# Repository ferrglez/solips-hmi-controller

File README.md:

# SOLIPS HMI Controller — Rev A

**Hardware design · KiCad · Engineering review pending**

> **Status:** Rev A design submitted for peer review. **Not approved for fabrication.** ERC/DRC were reported clean in the working KiCad project; electrical, mechanical and physical validation are still pending.

## Overview

SOLIPS HMI Controller Rev A is a dedicated four-layer PCB intended to offload the graphical human–machine interface (HMI) from an Arduino UNO Q host. The host provides semantic application data; the STM32 executes the graphical application locally and drives a GC9A01 circular TFT display.

The design follows the engineering baseline dated **30 September 2026**. That document freezes the major architecture but explicitly leaves component-specific verification and fabrication gates open. The current KiCad implementation must be compared with that baseline during review.

## System architecture

```text
Arduino UNO Q / QRB2210 (Debian)
           │ USB 2.0
           ▼
CP2102C-A01-GQFN24 (USB–UART bridge)
           │ USART1 · 3.3 V · PA9/PA10
           ▼
STM32U585CIT6 (LQFP48)
           │ SPI1 + DMA
           ▼
GC9A01 · 240 × 240 · RGB565
```

**Design rationale:** The UNO Q retains system and application logic, while the dedicated STM32 handles `VehicleState`, `UIManager`, LVGL and graphical assets. This reduces the HMI rendering workload on the host. Firmware migration and performance are **not yet demonstrated on this PCB**.

## Key engineering choices

| Subsystem | Rev A baseline | Rationale / verification |
| --- | --- | --- |
| Main MCU | STM32U585CIT6, LQFP48 | Dedicated local HMI processing; confirm package pinout, power domains and firmware budget |
| Host interface | CP2102C-A01-GQFN24 | USB–UART with DTR/RTS for planned boot/reset control; validate electrical implementation |
| Serial | USART1 on PA9/PA10 | Shared application communication and planned ROM bootloader update path |
| Display | GC9A01, 240×240, RGB565 | SPI1 + DMA, write-only interface; confirm actual module and connector pinout |
| Supply | USB 5 V input; 3.3 V LDO ≥500 mA | Simpler bring-up and no switching regulator; confirm load, inrush and thermal budget |
| Debug | SWD, manual BOOT/RESET | Recovery path independent of the USB bridge |
| PCB | 4 layers | Top signals/components, inner GND reference, inner power, bottom signals; verify actual stackup and return paths |

## KiCad project organization

The schematic is organized into five hierarchical sheets:

1. `01_POWER.kicad_sch` — USB input and regulation
2. `02_USB_UART.kicad_sch` — USB-C and CP2102C
3. `03_MCU.kicad_sch` — STM32 and boot/reset control
4. `04_DISPLAY.kicad_sch` — GC9A01 interface
5. `05_DEBUG.kicad_sch` — SWD and manual controls

The **current authoritative KiCad files** should be placed in `hardware/`, including the top-level `.kicad_sch`, `.kicad_pcb`, `.kicad_pro`, all five hierarchical sheets, and any required custom symbol/footprint libraries or board rules. The duplicate `- copia` folder is a local backup, not a second design release.

## Layout and routing

- Four-layer PCB with inner reference and power planes.
- Placement and routing performed in KiCad; FreeRouting was used as a routing aid, followed by manual completion and DRC cleanup.
- USB D+/D−, ground continuity, via transitions, connector orientation and mechanical fit still require an engineering review.
- The most recent DRC/ERC status was reported as clean by the designer; review the committed `DRC.rpt` / `ERC.rpt` and confirm they were generated **after the final edits**.

## Review checklist

- [ ] Cross-check actual KiCad schematic against STM32U585CIT6 and CP2102C manufacturer datasheets
- [ ] Verify USB-C CC resistors, ESD, USB data routing, shield and VBUS protection
- [ ] Verify MCU VDD/VDDA/VCAP and all decoupling connections
- [ ] Validate LDO part, USB current budget and worst-case thermal dissipation
- [ ] Verify DTR/RTS–BOOT0/NRST polarity, default states and STM32 option bytes
- [ ] Verify SWD header orientation and physical accessibility
- [ ] Confirm GC9A01 **actual module** pinout, supply, backlight and connector geometry/orientation
- [ ] Check actual four-layer stackup, copper returns, clearances and manufacturability
- [ ] Regenerate ERC/DRC on the final committed project
- [ ] Close fabrication gates FG-01 / FG-02 / FG-03 with evidence

## Planned validation

The baseline defines T01–T11: power, USB enumeration, UART, SWD, manual and automatic bootloader, CLI flashing, application boot, display, HMI screens and host protocol. **These are planned tests, not completed tests.**

## Documentation

- [`docs/Engineering_Specification.docx`](docs/Engineering_Specification.docx) — original engineering requirements and schematic baseline (v1.0, 2026-09-30).

## Review request

**Requested decision:** `APPROVED FOR NEXT STAGE` / `CHANGES REQUIRED` / `NOT APPROVED`.

**No fabrication order should be placed until the open electrical, mechanical and fabrication-gate checks are resolved.**

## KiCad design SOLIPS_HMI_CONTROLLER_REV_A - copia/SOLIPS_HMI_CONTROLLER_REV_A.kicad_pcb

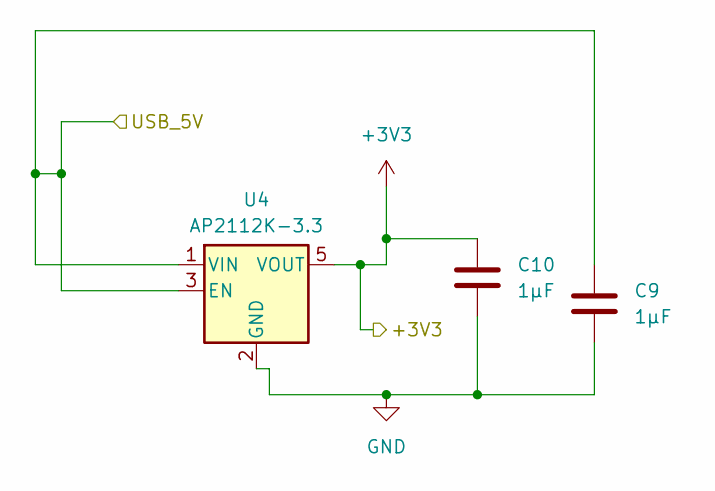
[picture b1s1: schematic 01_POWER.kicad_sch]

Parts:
C9, C10: 1µF; C_0805_2012Metric
U4: AP2112K-3.3; SOT-23-5

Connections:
+3V3: C10.1, U4.5 (VOUT); also elsewhere on the board
/02_USB_UART/USB_5V: C9.1, U4.1 (VIN), U4.3 (EN); also elsewhere on the board
GND: C9.2, C10.2, U4.2 (GND); also elsewhere on the board

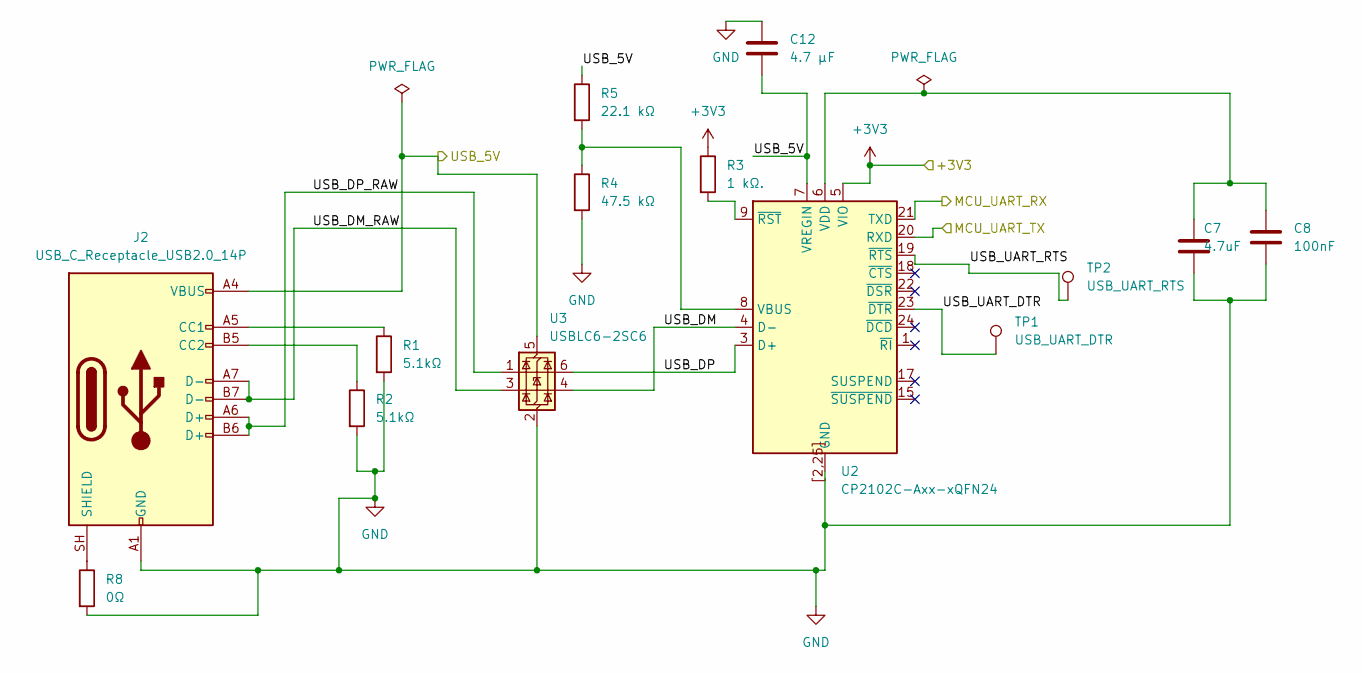
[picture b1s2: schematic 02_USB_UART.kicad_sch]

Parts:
C7: 4.7uF; C_0805_2012Metric
C8: 100nF; C_0603_1608Metric
C12: 4.7 µF; C_0805_2012Metric
J2: USB_C_Receptacle_USB2.0_14P; USB_C_Receptacle_Amphenol_124019772112A
R1, R2: 5.1kΩ; R_0603_1608Metric
R3: 1 kΩ.; R_0603_1608Metric
R4: 47.5 kΩ; R_0603_1608Metric
R5: 22.1 kΩ; R_0603_1608Metric
R8: 0Ω; R_0603_1608Metric
TP1: USB_UART_DTR; TestPoint_Pad_D1.5mm
TP2: USB_UART_RTS; TestPoint_Pad_D1.5mm
U2: CP2102C-Axx-xQFN24; WQFN-24-1EP_4x4mm_P0.5mm_EP2.45x2.45mm
U3: USBLC6-2SC6; SOT-23-6

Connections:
+3V3: R3.1, U2.5 (VIO); also elsewhere on the board
/02_USB_UART/MCU_UART_RX: U2.21 (TXD); also elsewhere on the board
/02_USB_UART/MCU_UART_TX: U2.20 (RXD); also elsewhere on the board
/02_USB_UART/USB_5V: C12.2, J2.A4 (VBUS), J2.A9 (VBUS), J2.B4 (VBUS), J2.B9 (VBUS), R5.1, U2.7 (VREGIN), U3.5 (VBUS); also elsewhere on the board
/02_USB_UART/USB_DM: U2.4 (D-), U3.4 (I/O2)
/02_USB_UART/USB_DM_RAW: J2.A7 (D-), J2.B7 (D-), U3.3 (I/O2); also elsewhere on the board
/02_USB_UART/USB_DP: U2.3 (D+), U3.6 (I/O1)
/02_USB_UART/USB_DP_RAW: J2.A6 (D+), J2.B6 (D+), U3.1 (I/O1); also elsewhere on the board
/02_USB_UART/USB_UART_DTR: TP1.1 (1_1), U2.23 (~DTR)
/02_USB_UART/USB_UART_RTS: TP2.1 (1_1), U2.19 (~RTS)
GND: C7.2, C8.2, C12.1, J2.A1 (GND), J2.A12 (GND), J2.B1 (GND), J2.B12 (GND), R1.2, R2.2, R4.2, R8.2, U2.2 (GND), U2.25 (GND), U2.[2,25] (GND), U3.2 (GND); also elsewhere on the board
unnamed 19: J2.A5 (CC1), R1.1; also elsewhere on the board
unnamed 20: J2.B5 (CC2), R2.1; also elsewhere on the board
unnamed 21: J2.SH (SHIELD), R8.1; also elsewhere on the board
unnamed: R4.1, R5.2, U2.8 (VBUS)
unnamed: C7.1, C8.1, U2.6 (VDD)
unnamed: R3.2, U2.9 (~RST)

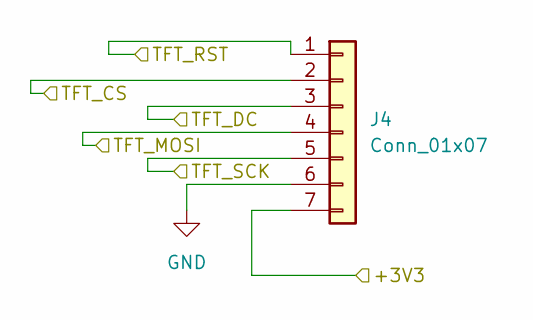
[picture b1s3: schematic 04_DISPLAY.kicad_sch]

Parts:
J4: Conn_01x07; PinHeader_1x07_P2.54mm_Vertical

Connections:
+3V3: J4.7; also elsewhere on the board
/03_MCu/TFT_CS: J4.2; also elsewhere on the board
/03_MCu/TFT_DC: J4.3; also elsewhere on the board
/03_MCu/TFT_MOSI: J4.4; also elsewhere on the board
/03_MCu/TFT_RST: J4.1; also elsewhere on the board
/03_MCu/TFT_SCK: J4.5; also elsewhere on the board
GND: J4.6; also elsewhere on the board

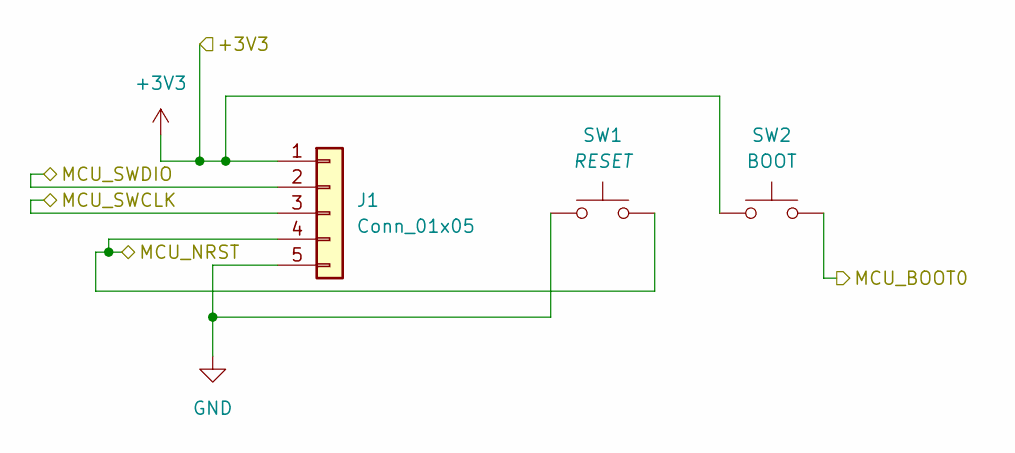
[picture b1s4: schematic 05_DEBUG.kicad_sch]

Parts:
J1: Conn_01x05; PinHeader_1x05_P2.54mm_Vertical
SW1: RESET; SW_SPST_TL3305A
SW2: BOOT; SW_SPST_TL3305A

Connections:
+3V3: J1.1, SW2.1; also elsewhere on the board
/03_MCu/MCU_BOOT0: SW2.2; also elsewhere on the board
/03_MCu/MCU_NRST: J1.3, J1.4, SW1.2; also elsewhere on the board
/03_MCu/MCU_SWDIO: J1.2; also elsewhere on the board
GND: J1.5, SW1.1; also elsewhere on the board

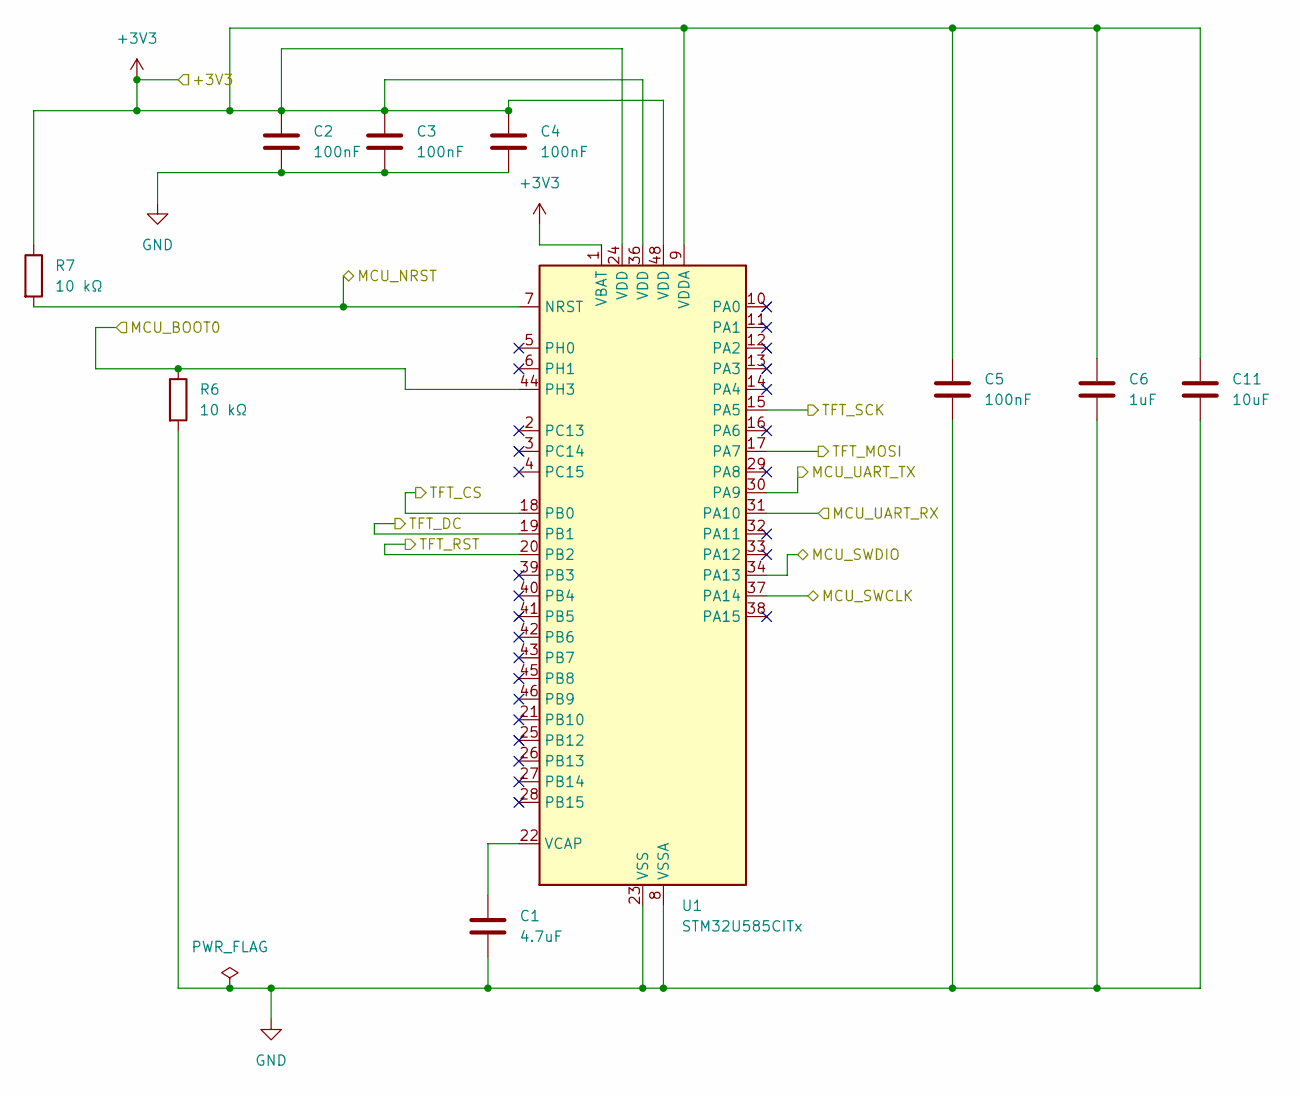
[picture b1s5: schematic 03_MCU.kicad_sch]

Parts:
C1: 4.7uF; C_0805_2012Metric
C2, C3, C4, C5: 100nF; C_0603_1608Metric
C6: 1uF; C_0805_2012Metric
C11: 10uF; C_1206_3216Metric
R6, R7: 10 kΩ; R_0603_1608Metric
U1: STM32U585CITx; LQFP-48_7x7mm_P0.5mm

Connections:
+3V3: C2.1, C3.1, C4.1, C5.1, C6.1, C11.1, R7.1, U1.1 (VBAT), U1.9 (VDDA), U1.24 (VDD), U1.36 (VDD), U1.48 (VDD); also elsewhere on the board
/02_USB_UART/MCU_UART_RX: U1.31 (PA10); also elsewhere on the board
/02_USB_UART/MCU_UART_TX: U1.30 (PA9); also elsewhere on the board
/03_MCu/MCU_BOOT0: R6.1, U1.44 (PH3); also elsewhere on the board
/03_MCu/MCU_NRST: R7.2, U1.7 (NRST), U1.37 (PA14); also elsewhere on the board
/03_MCu/MCU_SWDIO: U1.34 (PA13); also elsewhere on the board
/03_MCu/TFT_CS: U1.18 (PB0); also elsewhere on the board
/03_MCu/TFT_DC: U1.19 (PB1); also elsewhere on the board
/03_MCu/TFT_MOSI: U1.17 (PA7); also elsewhere on the board
/03_MCu/TFT_RST: U1.20 (PB2); also elsewhere on the board
/03_MCu/TFT_SCK: U1.15 (PA5); also elsewhere on the board
GND: C1.2, C2.2, C3.2, C4.2, C5.2, C6.2, C11.2, R6.2, U1.8 (VSSA), U1.23 (VSS), U1.35 (VSS), U1.47 (VSS); also elsewhere on the board
unnamed: C1.1, U1.22 (VCAP)

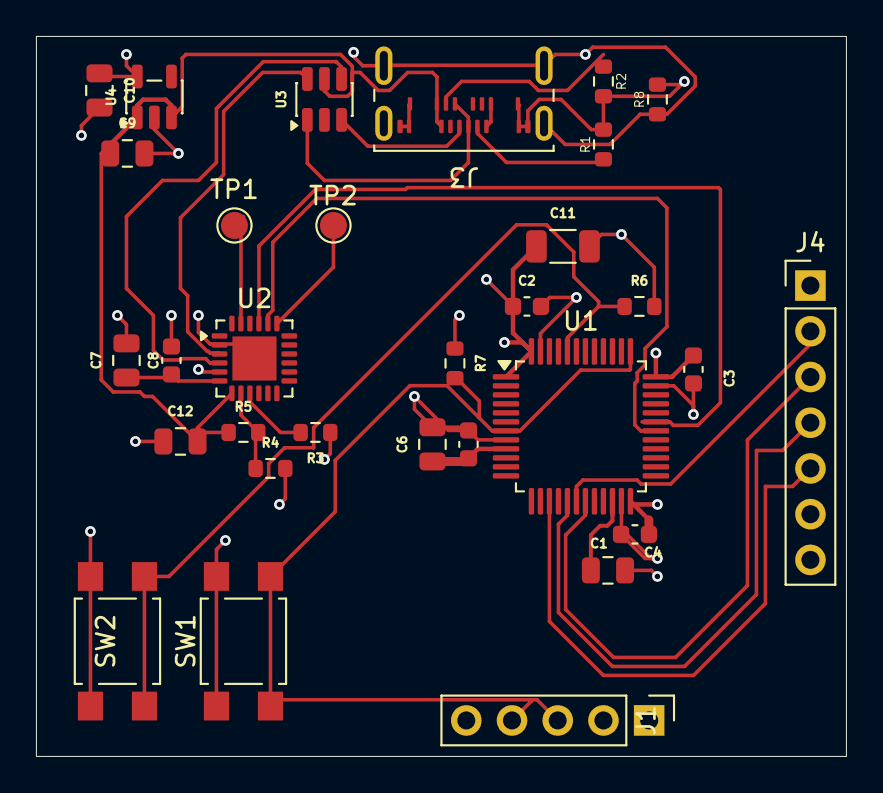
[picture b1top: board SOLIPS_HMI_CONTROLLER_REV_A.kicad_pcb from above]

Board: 4 copper layers, 45.0 x 40.0 mm, 31 parts (0 on the bottom side), 26 nets.

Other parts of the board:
J3: USB_C_Receptacle_USB2.0_16P; USB_C_Receptacle_Amphenol_124019772112A

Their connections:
/02_USB_UART/USB_5V: J3.A4 (VBUS), J3.A9 (VBUS), J3.B4 (VBUS), J3.B9 (VBUS); also elsewhere on the board
/02_USB_UART/USB_DM_RAW: J3.A7 (D-), J3.B7 (D-); also elsewhere on the board
/02_USB_UART/USB_DP_RAW: J3.A6 (D+), J3.B6 (D+); also elsewhere on the board
GND: J3.A1 (GND), J3.A12 (GND), J3.B1 (GND), J3.B12 (GND); also elsewhere on the board
unnamed 19: J3.A5 (CC1); also elsewhere on the board
unnamed 20: J3.B5 (CC2); also elsewhere on the board
unnamed 21: J3.SH (SHIELD); also elsewhere on the board
